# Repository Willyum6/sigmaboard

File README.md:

# sigmaboard
My hackclub blueprint keyboard 

Contains:
- 3 separate printed parts
- 4 M3 bolts and 4 inserts
- 6 keys total
- 128x32 OLED screen
- 2 WS2812B RGB LEDs as underglow beneath the keys and the slits on the right
- 1 XIAO RP2040
- 6 diodes
- a very cool name

  ______________

  CAD:
  3 parts: a bottom case, a middle plate to define the keyholes, and a top cover which has slits to let LEDs shine through, keyspaces, and an opening for the OLED

WITHOUT 3rd LAYER: 

WITHOUT 3RD AND 2ND layer: 

  (made in fusion360)

  ________________

  PCB and Schematic:

  PCB:

Schematic:

__________________

FIRMWARE:
Sigmaboard uses QMK.
Keys act as arrow keys, with the two oriented on the right in a stack operate as "enter" and "shift"(to play games)
OLED screen should display an animation of bones ( that I created from scrath in Photoshop) moving across the screen:

_______________

BOM:
- 6 Cherry MX Switches
- 6 DSA Keycaps
- 4 M3x12mm SHCS Bolts
- 4 M3x5x4 Heatset inserts
- 1 XIAO RP2040
- 1 0.91" 128x32 OLED Display
- 2 WS2812B LEDs
- 6 DO-35 diodes

_______________________
Final notes:
I spent a long time on this project and am very proud of it, I would love to get it approved and test it out in person! 
I learnt a lot about the cadding process, as well as about PCB and the parts needed for projects like keyboards. 
I will say I feel I didn't learn enough about understanding the code, but it is something I definitely will do once I can test out my keyboard.

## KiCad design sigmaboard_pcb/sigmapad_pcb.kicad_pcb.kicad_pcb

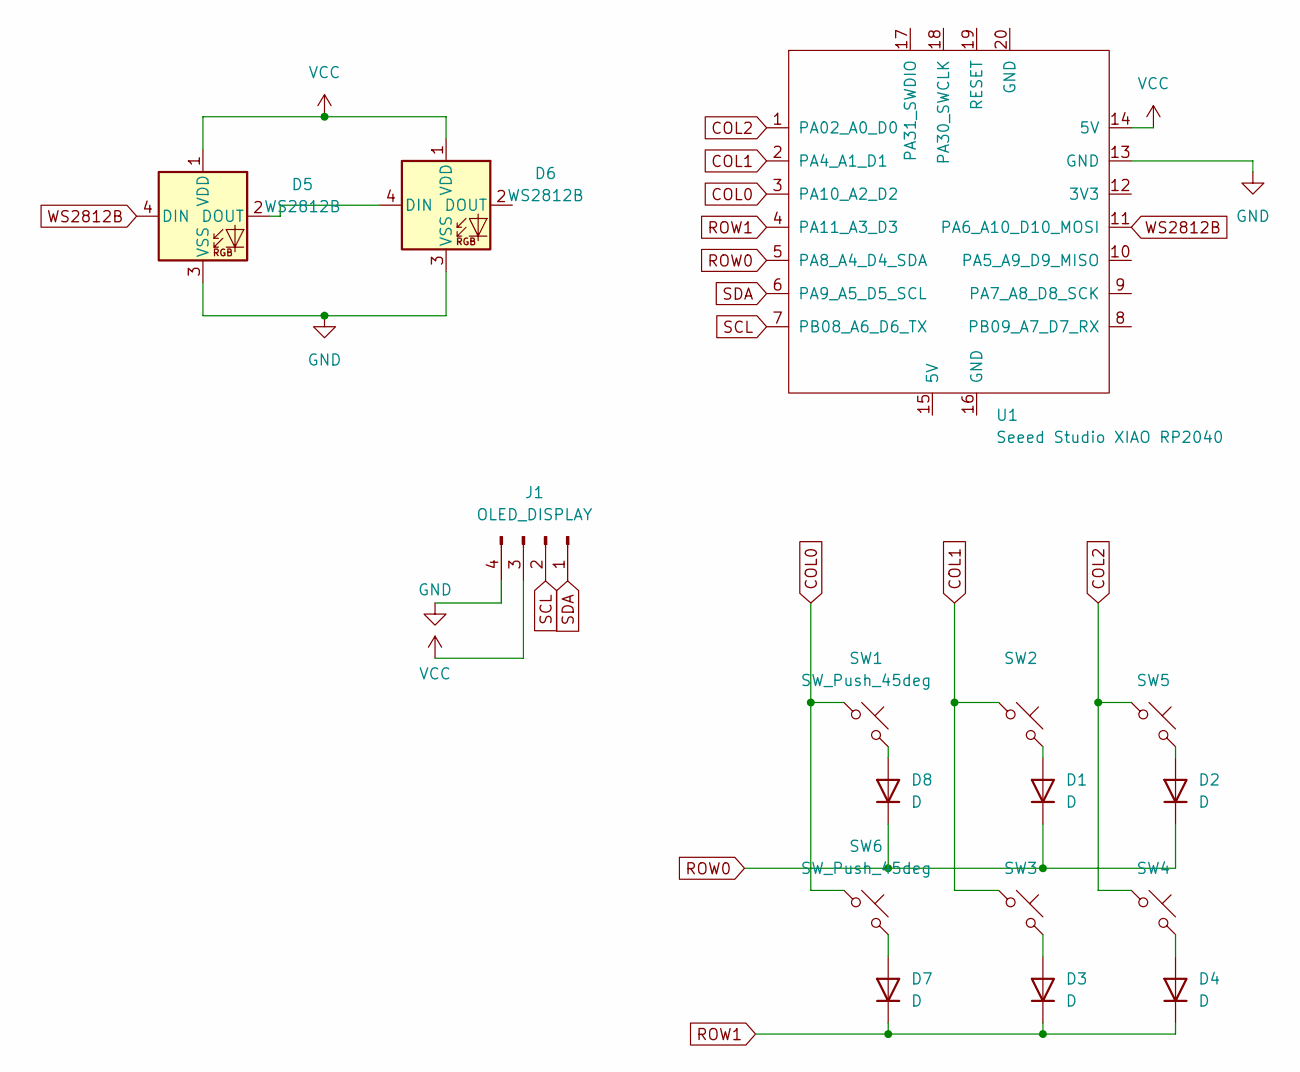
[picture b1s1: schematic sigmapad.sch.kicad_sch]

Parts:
D1, D2, D3, D4, D7, D8: D; D_DO-35_SOD27_P7.62mm_Horizontal
D5, D6: WS2812B; LED_WS2812B_PLCC4_5.0x5.0mm_P3.2mm
J1: OLED_DISPLAY; PinHeader_1x04_P2.54mm_Vertical
SW1, SW2, SW3, SW4, SW5, SW6: SW_Push_45deg; MX-Solderable-1U
U1: Seeed Studio XIAO RP2040; XIAO-RP2040-SMD

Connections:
COL0: SW1.1, SW6.1, U1.3 (PA10_A2_D2)
COL1: SW2.1, SW3.1, U1.2 (PA4_A1_D1)
COL2: SW4.1, SW5.1, U1.1 (PA02_A0_D0)
GND: D5.3 (VSS), D6.3 (VSS), J1.4, U1.13 (GND)
unnamed: D1.2 (A), SW2.2
unnamed: D2.2 (A), SW5.2
unnamed: D3.2 (A), SW3.2
unnamed: D4.2 (A), SW4.2
unnamed: D5.2 (DOUT), D6.4 (DIN)
unnamed: D7.2 (A), SW6.2
unnamed: D8.2 (A), SW1.2
ROW0: D1.1 (K), D2.1 (K), D8.1 (K), U1.5 (PA8_A4_D4_SDA)
ROW1: D3.1 (K), D4.1 (K), D7.1 (K), U1.4 (PA11_A3_D3)
SCL: J1.2, U1.7 (PB08_A6_D6_TX)
SDA: J1.1, U1.6 (PA9_A5_D5_SCL)
VCC: D5.1 (VDD), D6.1 (VDD), J1.3, U1.14 (5V)
WS2812B: D5.4 (DIN), U1.11 (PA6_A10_D10_MOSI)

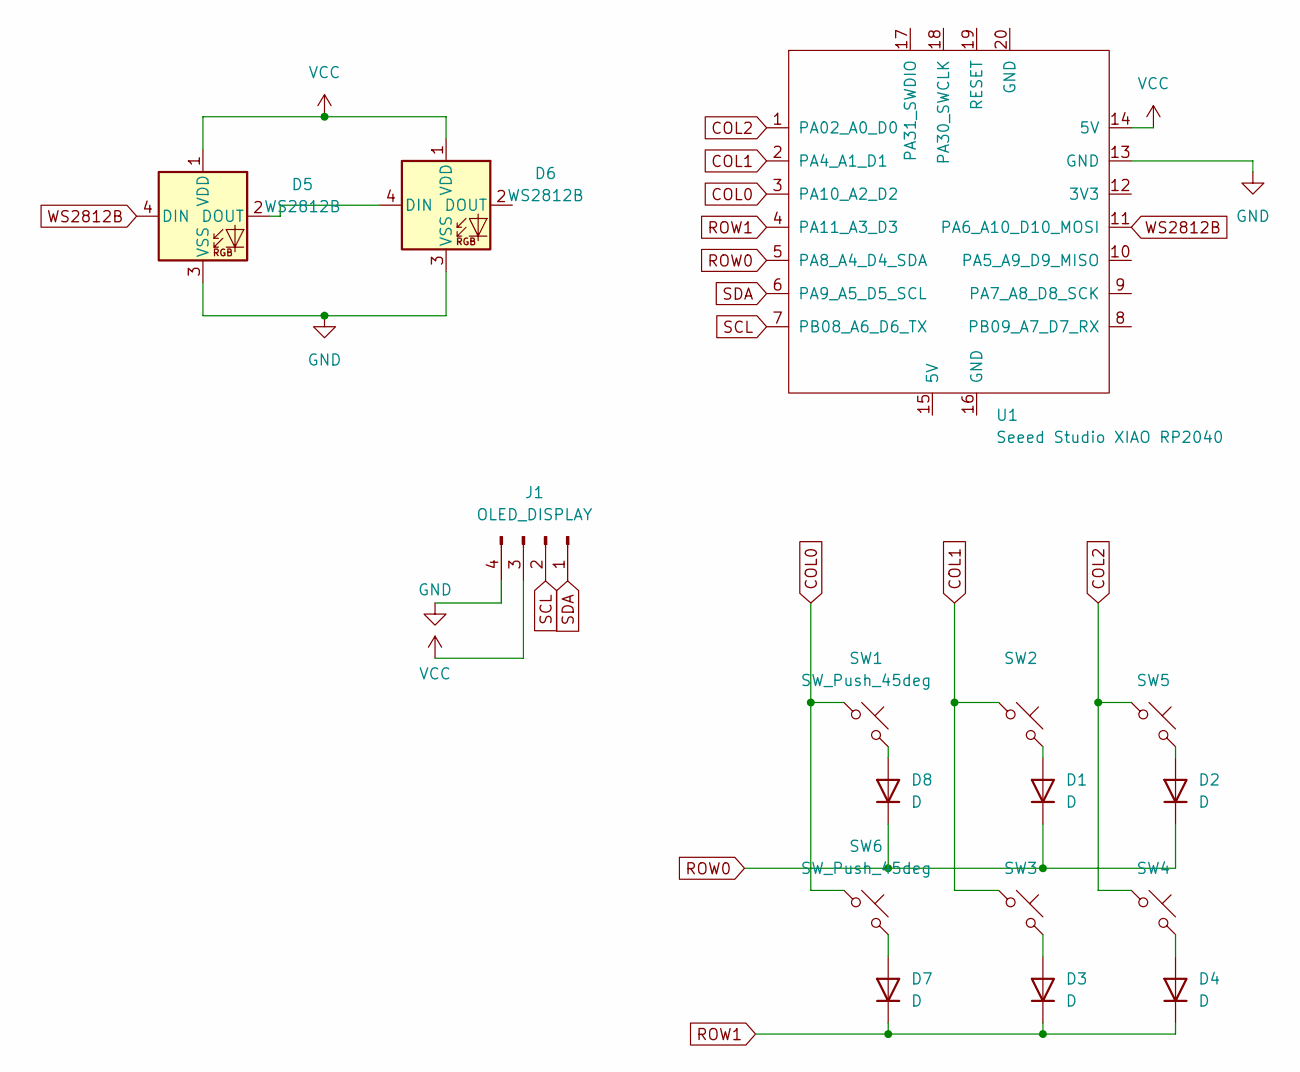
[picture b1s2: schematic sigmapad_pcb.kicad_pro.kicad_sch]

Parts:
D1, D2, D3, D4, D7, D8: D; D_DO-35_SOD27_P7.62mm_Horizontal
D5, D6: WS2812B; LED_WS2812B_PLCC4_5.0x5.0mm_P3.2mm
J1: OLED_DISPLAY; PinHeader_1x04_P2.54mm_Vertical
SW1, SW2, SW3, SW4, SW5, SW6: SW_Push_45deg; MX-Solderable-1U
U1: Seeed Studio XIAO RP2040; XIAO-RP2040-SMD

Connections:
COL0: SW1.1, SW6.1, U1.3 (PA10_A2_D2)
COL1: SW2.1, SW3.1, U1.2 (PA4_A1_D1)
COL2: SW4.1, SW5.1, U1.1 (PA02_A0_D0)
GND: D5.3 (VSS), D6.3 (VSS), J1.4, U1.13 (GND)
unnamed: D1.2 (A), SW2.2
unnamed: D2.2 (A), SW5.2
unnamed: D3.2 (A), SW3.2
unnamed: D4.2 (A), SW4.2
unnamed: D5.2 (DOUT), D6.4 (DIN)
unnamed: D7.2 (A), SW6.2
unnamed: D8.2 (A), SW1.2
ROW0: D1.1 (K), D2.1 (K), D8.1 (K), U1.5 (PA8_A4_D4_SDA)
ROW1: D3.1 (K), D4.1 (K), D7.1 (K), U1.4 (PA11_A3_D3)
SCL: J1.2, U1.7 (PB08_A6_D6_TX)
SDA: J1.1, U1.6 (PA9_A5_D5_SCL)
VCC: D5.1 (VDD), D6.1 (VDD), J1.3, U1.14 (5V)
WS2812B: D5.4 (DIN), U1.11 (PA6_A10_D10_MOSI)

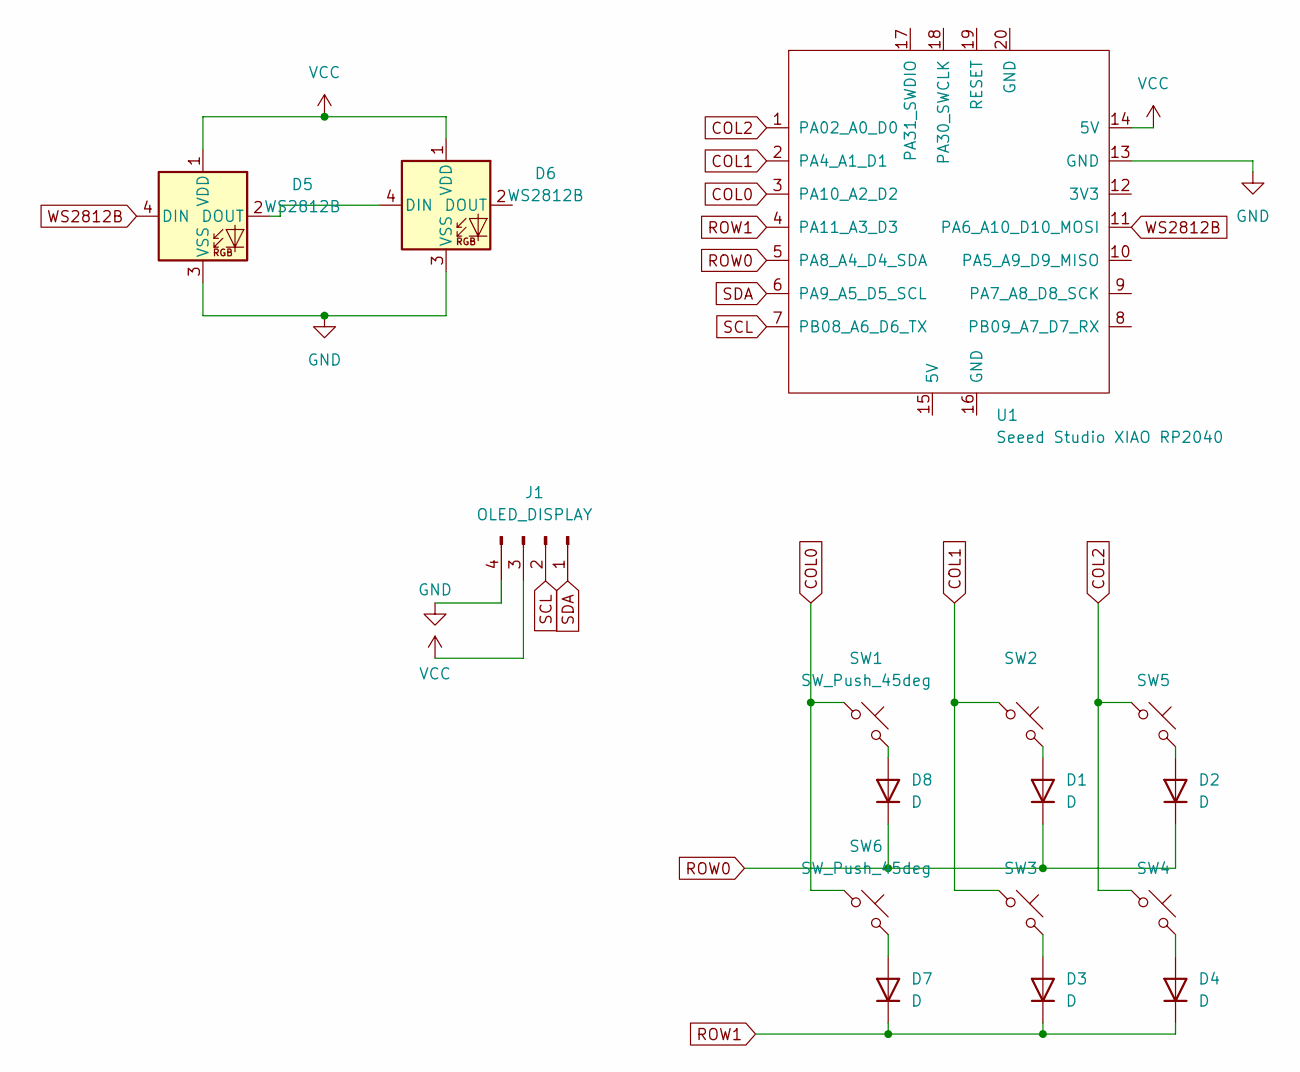
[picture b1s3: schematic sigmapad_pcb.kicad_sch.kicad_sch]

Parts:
D1, D2, D3, D4, D7, D8: D; D_DO-35_SOD27_P7.62mm_Horizontal
D5, D6: WS2812B; LED_WS2812B_PLCC4_5.0x5.0mm_P3.2mm
J1: OLED_DISPLAY; PinHeader_1x04_P2.54mm_Vertical
SW1, SW2, SW3, SW4, SW5, SW6: SW_Push_45deg; MX-Solderable-1U
U1: Seeed Studio XIAO RP2040; XIAO-RP2040-SMD

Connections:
COL0: SW1.1, SW6.1, U1.3 (PA10_A2_D2)
COL1: SW2.1, SW3.1, U1.2 (PA4_A1_D1)
COL2: SW4.1, SW5.1, U1.1 (PA02_A0_D0)
GND: D5.3 (VSS), D6.3 (VSS), J1.4, U1.13 (GND)
unnamed: D1.2 (A), SW2.2
unnamed: D2.2 (A), SW5.2
unnamed: D3.2 (A), SW3.2
unnamed: D4.2 (A), SW4.2
unnamed: D5.2 (DOUT), D6.4 (DIN)
unnamed: D7.2 (A), SW6.2
unnamed: D8.2 (A), SW1.2
ROW0: D1.1 (K), D2.1 (K), D8.1 (K), U1.5 (PA8_A4_D4_SDA)
ROW1: D3.1 (K), D4.1 (K), D7.1 (K), U1.4 (PA11_A3_D3)
SCL: J1.2, U1.7 (PB08_A6_D6_TX)
SDA: J1.1, U1.6 (PA9_A5_D5_SCL)
VCC: D5.1 (VDD), D6.1 (VDD), J1.3, U1.14 (5V)
WS2812B: D5.4 (DIN), U1.11 (PA6_A10_D10_MOSI)

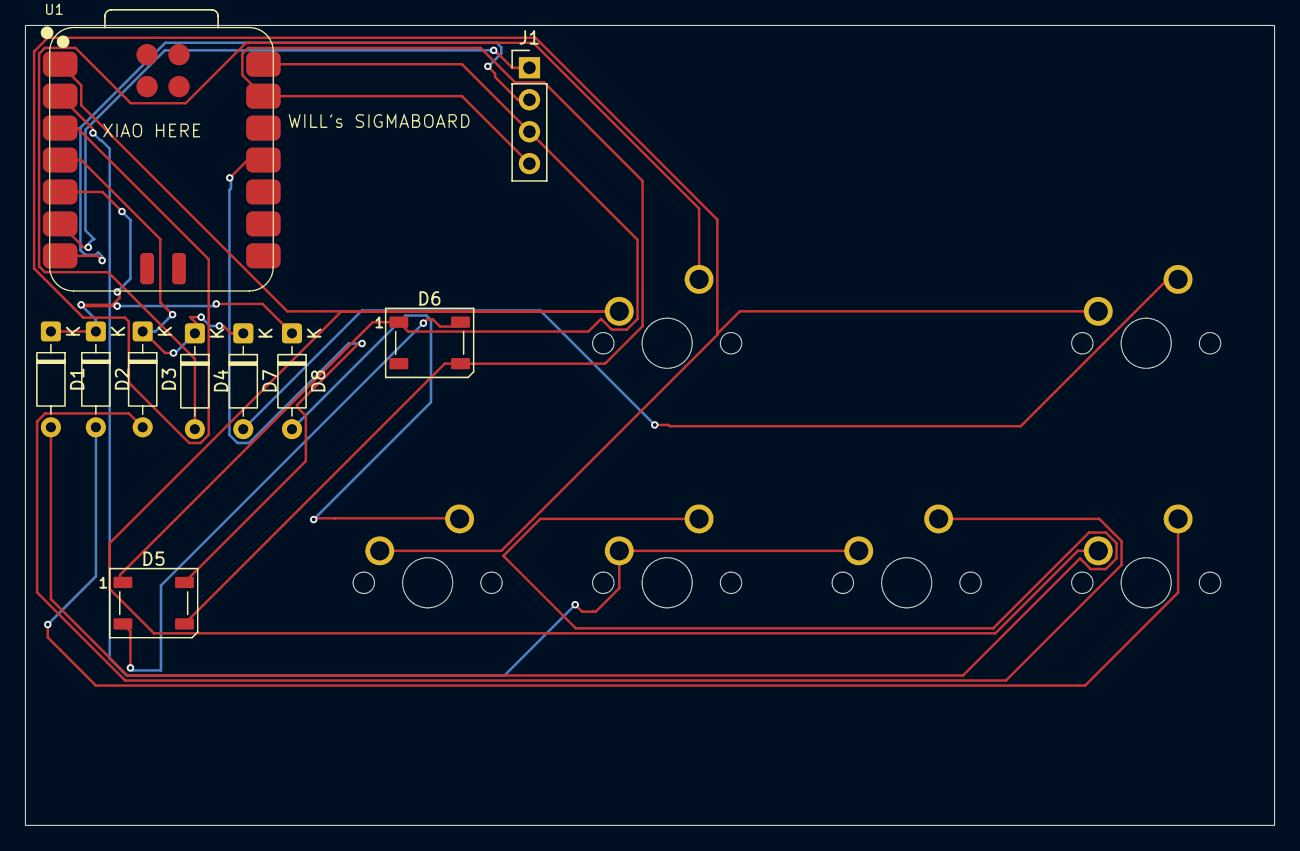
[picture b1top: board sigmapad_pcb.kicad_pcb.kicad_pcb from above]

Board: 2 copper layers, 99.3 x 63.6 mm, 16 parts (0 on the bottom side), 17 nets.

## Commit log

2025-12-25 Create pcb
